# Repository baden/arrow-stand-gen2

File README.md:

# arrow-stand-gen2 — бездрововий датчик влучання в мішень

Пристрій, що кріпиться на мішень, фіксує удар (акселерометр), і бездрово передає
факт влучання на базову станцію (приймач) за LoRa.

**Мета проєкту — мінімально можлива собівартість.** Пристрій розхідний: він
отримує удари і, можливо, знищується під час стрільби. Тому критерії відбору
компонентів — не «найкраще», а «дешевше, при цьому працює».

## Поточний стан

| Блок | Статус | Рішення |
|---|---|---|
| Радіо | Обрано | SX1262IMLTRT, 150–960 МГц, +22 dBm, $1.91 @100 шт |
| МК | Обрано | **CH32V203F8U6** (QFN-20), 64 KB Flash / 20 KB SRAM, 144 МГц, $0.39 @100 шт — див. [ADR-0007](docs/adr/0007-mcu-and-radio.md) |
| Акселерометр | Кандидат | SC7A20HTR, ±16 g, LGA-12, $0.20 @100 шт — див. [ADR-0003](docs/adr/0003-accelerometer.md) |
| Живлення | Кандидат | LiPo 3.7 В → ME6211C33M5G-N (3.3 В LDO, $0.051) + TP4056 ($0.148) |
| Антена | Обрано | **SMA + зовнішня антена** (обов'язково для >1 км) — див. [ADR-0004](docs/adr/0004-antenna.md) |
| Прошивка | Не розпочато | RISC-V (WCH), toolchain MounRiver; конвеєр аналізу на пристрої — [ADR-0008](docs/adr/0008-ondevice-analysis-and-hub.md) |
| Хаб | Спроєктовано | те саме залізо: CH32V203F8U6 + SX1262 у RX + USB-C — [ADR-0008](docs/adr/0008-ondevice-analysis-and-hub.md) |
| Частота радіо | Обрано | **433 МГц** — ліс і холми, найкраще проникнення й запас чутливості — див. [ADR-0005](docs/adr/0005-radio-band.md) |

## Орієнтовна собівартість (за 100 шт.)

Ціни — **цінова сходинка LCSC при замовленні 100 шт.** (2026-11-18).

```
PCB 2 шари, 35×40 мм .............. $0.35
SX1262IMLTRT ....................... $1.91
CH32V203F8U6 ....................... $0.39
SC7A20HTR ......................... $0.20
TP4056-42-ESOP8 .................... $0.15
Кристал 32 МГц ..................... $0.10
ME6211C33M5G-N ..................... $0.05
Пасивні (~8 шт) + кнопка ......... $0.06
                                  ─────────
                        Разом:    ≈ $3.21  (без монтажу)
```

Деталі — у [docs/cost/budget.md](docs/cost/budget.md).
Зняття цін: `python3 tools/lcsc_prices.py --from-bom hardware/bom/bom-draft.csv --qty 100 --update-bom`.

## Структура репозиторію

```
docs/            документація: вимоги, архітектура, ADR, план дослідження, вартість
                 architecture/schematic-spec.md — специфікація схеми мішені
                 hub/hub-requirements.md   — початкове ТЗ хаба
hardware/        target/ + hub/ (проєкти KiCAD), BOM, механіка, збірка
firmware/        common/ (спільне), target/ (мішень), hub/ (хаб)
tools/           допоміжні скрипти
.opencode/       проєктні скіли та агент для ШІ
```

## Швидкий старт для агента

Прочитай [AGENTS.md](AGENTS.md) — це обов'язковий інструктаж перед будь-якою
роботою в репозиторії. Там же — маршрутизація інструментів Copperpour і
правила «дешево».

## Ліцензії та походження

Компоненти — з LCSC/JLCPCB. Перед серійною парттією перевірити локальні
регуляторні вимоги до діапазону й потужності передавача (ETSI EN 300 220 /
FCC Part 15) та правила літій на зони ураження.

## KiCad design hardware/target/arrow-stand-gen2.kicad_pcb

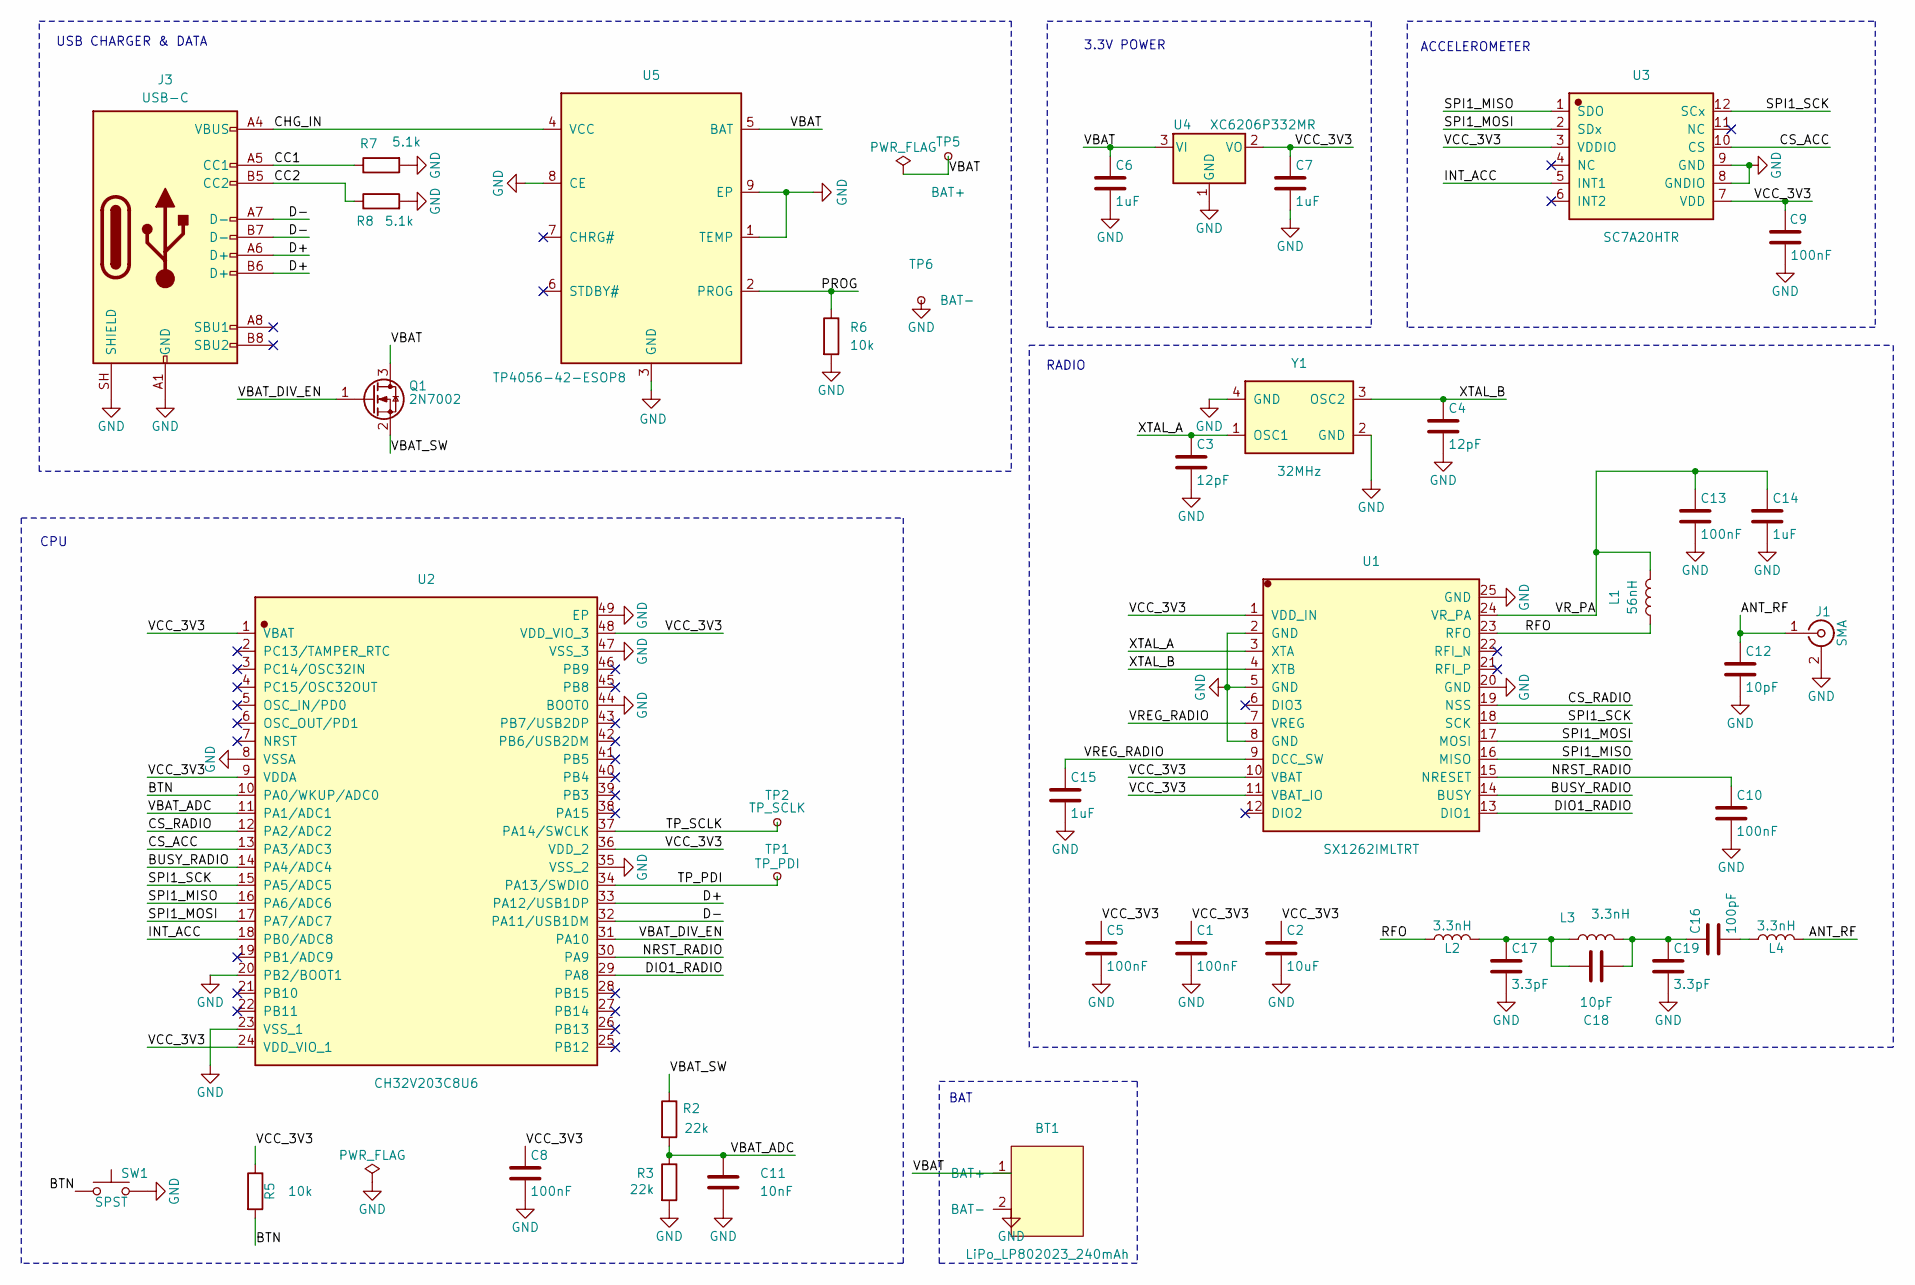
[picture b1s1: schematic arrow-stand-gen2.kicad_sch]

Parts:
BT1: LiPo_LP802023_240mAh; MPN LP802023
C1, C5, C8, C9, C10, C13: 100nF; C_0402_1005Metric; MPN CL05B104KO5NNNC; LCSC C1525
C2: 10uF; C_0805_2012Metric; MPN CL21A106KAYNNNE; LCSC C15850
C3, C4: 12pF; C_0402_1005Metric; MPN 0402CG120J500NT; LCSC C1547
C6, C7, C14, C15: 1uF; C_0402_1005Metric; MPN CL05A105KA5NQNC; LCSC C52923
C11: 10nF; C_0402_1005Metric; MPN CL05B103KB5NNNC; LCSC C15195
C12, C18: 10pF; C_0402_1005Metric; MPN CL05C100JB5NNNC; LCSC C32949
C16: 100pF; C_0402_1005Metric; MPN 0402CG101J500NT; LCSC C1546
C17, C19: 3.3pF; C_0402_1005Metric; MPN 0402CG3R3C500NT; LCSC C1565
J1: SMA; SMA_Amphenol_132134_Vertical; MPN HL-SMA-KE-02; LCSC C20617215
J3: USB-C; USB_C_Receptacle_HRO_TYPE-C-31-M-12; MPN TYPE-C-31-M-12; LCSC C165948
L1: 56nH; L_0402_1005Metric; MPN LQW15AN56NG80D; LCSC C1330587
L2, L3, L4: 3.3nH; L_0402_1005Metric; MPN VHF100505HQ3N3BT; LCSC C3032779
Q1: 2N7002; SOT-23; MPN 2N7002; LCSC C8545
R2, R3: 22k; R_0402_1005Metric; MPN 0402WGF2202TCE; LCSC C25768
R5, R6: 10k; R_0402_1005Metric; MPN 0402WGF1002TCE; LCSC C25744
R7, R8: 5.1k; R_0402_1005Metric; MPN 0402WGF5101TCE; LCSC C25905
SW1: SPST; SW_SPST_B3U-1000P; MPN B3U-1000P; LCSC C231329
TP1: TP_PDI; TestPoint_Pad_1.0x1.0mm
TP2: TP_SCLK; TestPoint_Pad_1.0x1.0mm
TP5: BAT+; TestPoint_Pad_1.0x1.0mm
TP6: BAT-; TestPoint_Pad_1.0x1.0mm
U1: SX1262IMLTRT; QFN-24_L4.0-W4.0-P0.50-BL-EP2.6; MPN SX1262IMLTRT; JLCPCB_Class Extended Part
U2: CH32V203C8U6; TQFN-48_L7.0-W7.0-P0.50-BL-EP5.5; MPN CH32V203C8U6; JLCPCB_Class Extended Part
U3: SC7A20HTR; LGA-12_L2.0-W2.0-P0.50-TL; MPN SC7A20HTR; JLCPCB_Class Extended Part
U4: XC6206P332MR; SOT-23-3; MPN XC6206P332MR; LCSC C2897477
U5: TP4056-42-ESOP8; ESOP-8_L4.9-W3.9-P1.27-LS6.0-BL-EP; MPN TP4056-42-ESOP8; JLCPCB_Class Extended Part
Y1: 32MHz; CRYSTAL-SMD_4P-L3.2-W2.5-BL; MPN E3SB32E00000KE; JLCPCB_Class Extended Part

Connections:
/ANT_RF: C12.1, J1.1 (In), L4.2
/BTN: R5.2, SW1.1, U2.10 (PA0/WKUP/ADC0)
/BUSY_RADIO: U1.14 (BUSY), U2.14 (PA4/ADC4)
/CC1: J3.A5 (CC1), R7.1
/CC2: J3.B5 (CC2), R8.1
/CHG_IN: J3.A4 (VBUS), J3.A9 (VBUS), J3.B4 (VBUS), J3.B9 (VBUS), U5.4 (VCC)
/CS_ACC: U2.13 (PA3/ADC3), U3.10 (CS)
/CS_RADIO: U1.19 (NSS), U2.12 (PA2/ADC2)
/D+: J3.A6 (D+), J3.B6 (D+), U2.33 (PA12/USB1DP)
/D-: J3.A7 (D-), J3.B7 (D-), U2.32 (PA11/USB1DM)
/DIO1_RADIO: U1.13 (DIO1), U2.29 (PA8)
/INT_ACC: U2.18 (PB0/ADC8), U3.5 (INT1)
/NRST_RADIO: C10.1, U1.15 (NRESET), U2.30 (PA9)
/PROG: R6.1, U5.2 (PROG)
/RFO: L1.2, L2.1, U1.23 (RFO)
/SPI1_MISO: U1.16 (MISO), U2.16 (PA6/ADC6), U3.1 (SDO)
/SPI1_MOSI: U1.17 (MOSI), U2.17 (PA7/ADC7), U3.2 (SDx)
/SPI1_SCK: U1.18 (SCK), U2.15 (PA5/ADC5), U3.12 (SCx)
/TP_PDI: TP1.1 (1_1), U2.34 (PA13/SWDIO)
/TP_SCLK: TP2.1 (1_1), U2.37 (PA14/SWCLK)
/VBAT: BT1.1 (BAT+), C6.1, Q1.3 (D), TP5.1 (1_1), U4.3 (VI), U5.5 (BAT)
/VBAT_ADC: C11.1, R2.2, R3.1, U2.11 (PA1/ADC1)
/VBAT_DIV_EN: Q1.1 (G), U2.31 (PA10)
/VBAT_SW: Q1.2 (S), R2.1
/VCC_3V3: C1.1, C2.1, C5.1, C7.1, C8.1, C9.1, R5.1, U1.1 (VDD_IN), U1.10 (VBAT), U1.11 (VBAT_IO), U2.1 (VBAT), U2.9 (VDDA), U2.24 (VDD_VIO_1), U2.36 (VDD_2), U2.48 (VDD_VIO_3), U3.3 (VDDIO), U3.7 (VDD), U4.2 (VO)
/VREG_RADIO: C15.1, U1.7 (VREG), U1.9 (DCC_SW)
/VR_PA: C13.1, C14.1, L1.1, U1.24 (VR_PA)
/XTAL_A: C3.1, U1.3 (XTA), Y1.1 (OSC1)
/XTAL_B: C4.1, U1.4 (XTB), Y1.3 (OSC2)
GND: BT1.2 (BAT-), C1.2, C2.2, C3.2, C4.2, C5.2, C6.2, C7.2, C8.2, C9.2, C10.2, C11.2, C12.2, C13.2, C14.2, C15.2, C17.2, C19.2, J1.2 (Ext), J3.A1 (GND), J3.A12 (GND), J3.B1 (GND), J3.B12 (GND), J3.SH (SHIELD), R3.2, R6.2, R7.2, R8.2, SW1.2, TP6.1 (1_1), U1.2 (GND), U1.5 (GND), U1.8 (GND), U1.20 (GND), U1.25 (GND), U2.8 (VSSA), U2.20 (PB2/BOOT1), U2.23 (VSS_1), U2.35 (VSS_2), U2.44 (BOOT0), U2.47 (VSS_3), U2.49 (EP), U3.8 (GNDIO), U3.9 (GND), U4.1 (GND), U5.1 (TEMP), U5.3 (GND), U5.8 (CE), U5.9 (EP), Y1.2 (GND), Y1.4 (GND)
unnamed: C16.1, C18.2, C19.1, L3.2
unnamed: C16.2, L4.1
unnamed: C17.1, C18.1, L2.2, L3.1

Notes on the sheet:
BAT
3.3V POWER
CPU
ACCELEROMETER
RADIO
USB CHARGER & DATA

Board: 2 copper layers, 44 parts (0 on the bottom side), 33 nets, no tracks yet.

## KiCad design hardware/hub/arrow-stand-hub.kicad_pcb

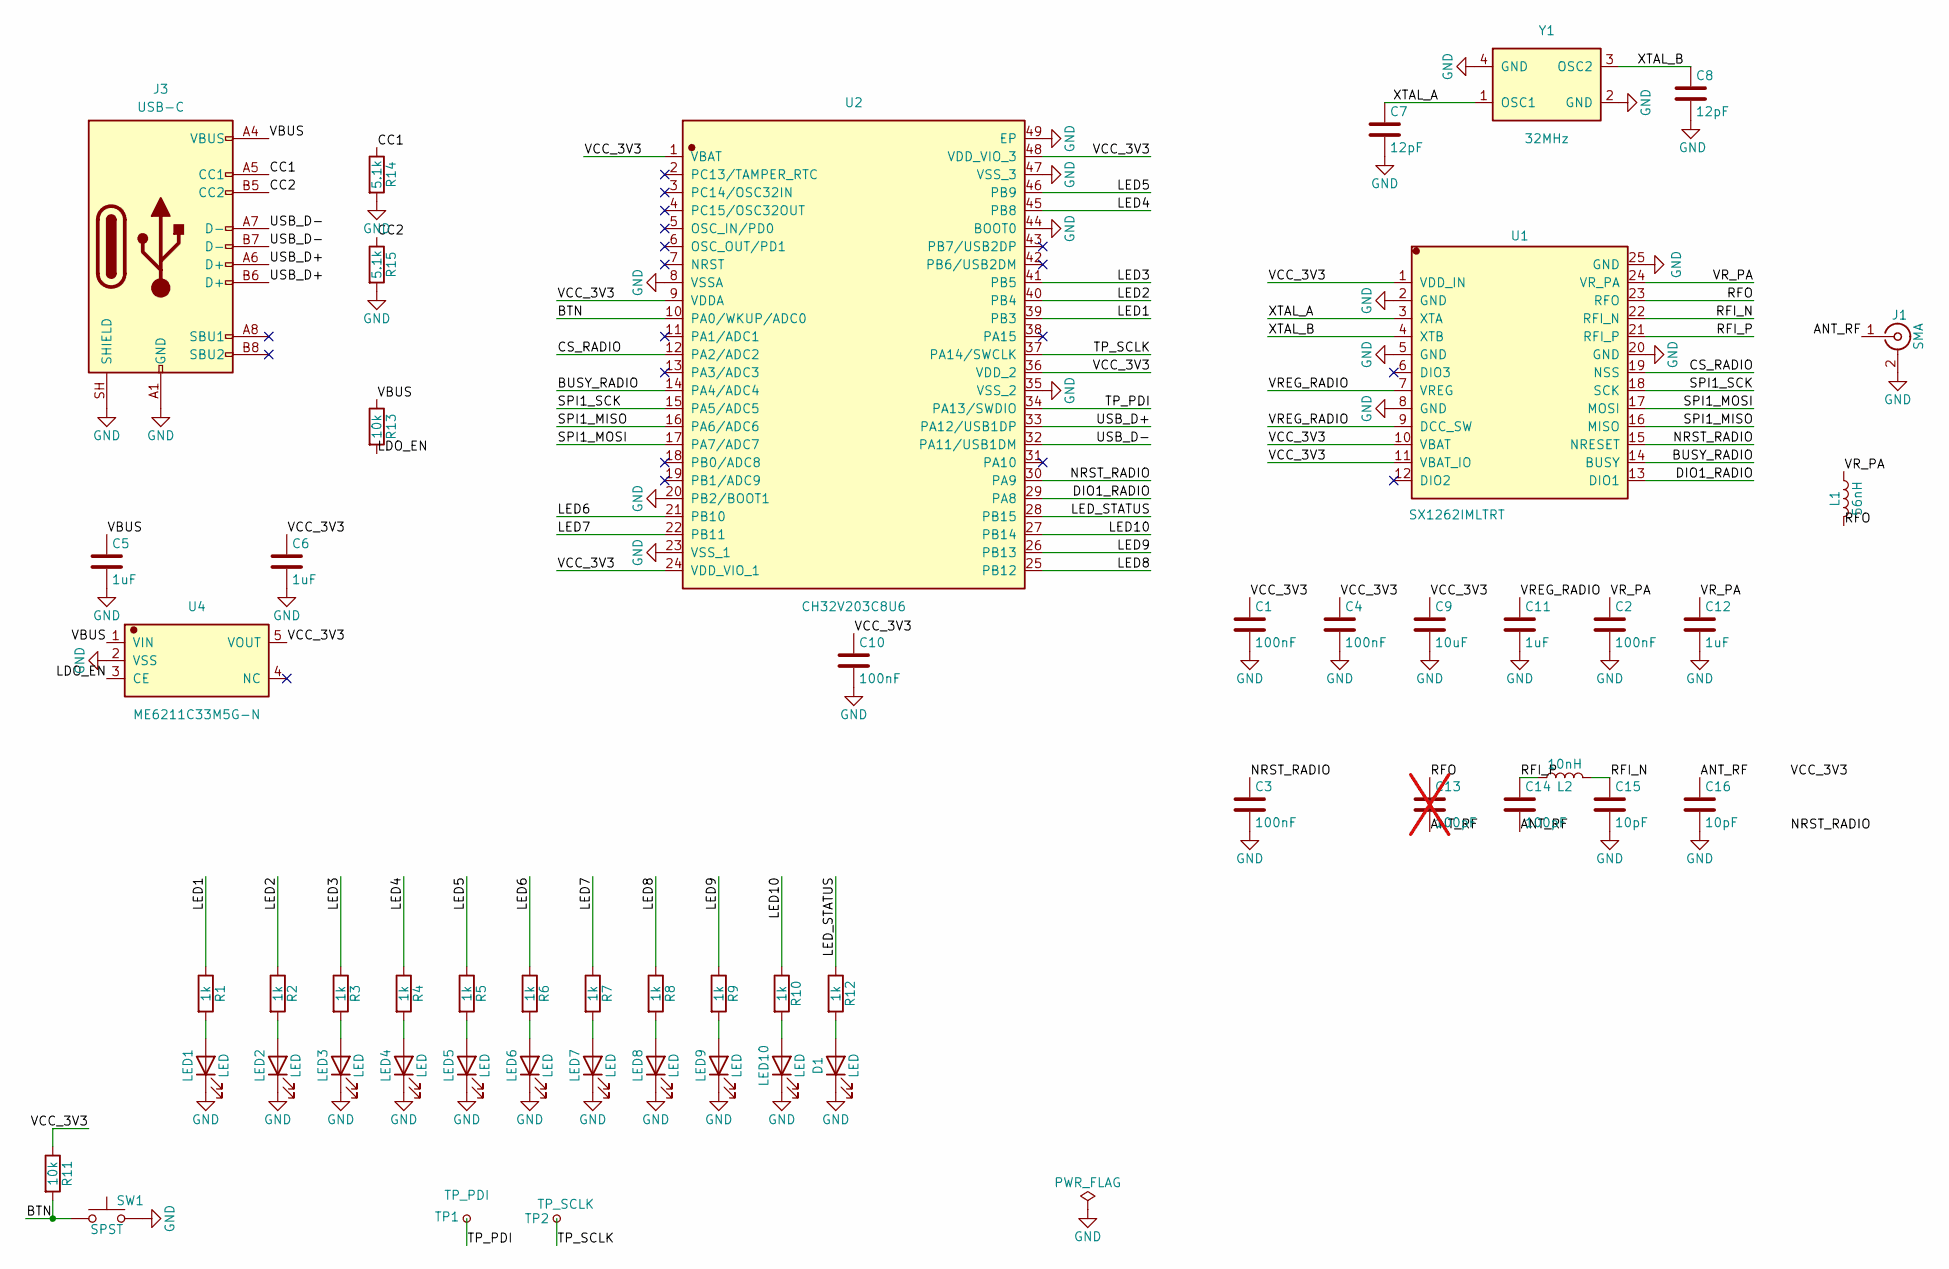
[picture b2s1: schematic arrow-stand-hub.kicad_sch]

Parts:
C1, C3, C4, C10: 100nF; C_0402_1005Metric; MPN CL05B104KO5NNNC; LCSC C1525
C2: 100nF; C_0402_1005Metric
C5, C6, C11, C12: 1uF; C_0402_1005Metric; MPN CL05A105KA5NQNC; LCSC C52923
C7, C8: 12pF; C_0402_1005Metric; MPN 0402CG120J500NT; LCSC C1547
C9: 10uF; C_0805_2012Metric; MPN CL21A106KAYNNNE; LCSC C15850
C13: 100pF; C_0402_1005Metric; MPN 0402CG101J500NT; LCSC C1546; not fitted
C14: 100pF; C_0402_1005Metric; MPN 0402CG101J500NT; LCSC C1546
C15, C16: 10pF; C_0402_1005Metric; MPN CL05C100JB5NNNC; LCSC C32949
D1: LED; LED_0805_2012Metric; MPN D-G080508G1-KS2; LCSC C107402
J1: SMA; SMA_Amphenol_132289_EdgeMount
J3: USB-C; USB_C_Receptacle_HRO_TYPE-C-31-M-12; MPN TYPE-C-31-M-12; LCSC C165948
L1: 56nH; L_0402_1005Metric
L2: 10nH; L_0402_1005Metric; MPN VHF100505HQ10NJT; LCSC C395047
LED1, LED2, LED3, LED4, LED5, LED6, LED7, LED8, LED9, LED10: LED; LED_0805_2012Metric; MPN D-G080508G1-KS2; LCSC C107402
R1, R2, R3, R4, R5, R6, R7, R8, R9, R10, R12: 1k; R_0402_1005Metric; MPN CR0402FF1001G; LCSC C100195
R11, R13: 10k; R_0402_1005Metric; MPN 0402WGF1002TCE; LCSC C25744
R14, R15: 5.1k; R_0402_1005Metric; MPN 0402WGF5101TCE; LCSC C25905
SW1: SPST; SW_SPST_B3U-1000P
TP1: TP_PDI; TestPoint_Pad_1.0x1.0mm
TP2: TP_SCLK; TestPoint_Pad_1.0x1.0mm
U1: SX1262IMLTRT; QFN-24_L4.0-W4.0-P0.50-BL-EP2.6; MPN SX1262IMLTRT; JLCPCB_Class Extended Part
U2: CH32V203C8U6; TQFN-48_L7.0-W7.0-P0.50-BL-EP5.5; MPN CH32V203C8U6; JLCPCB_Class Extended Part
U4: ME6211C33M5G-N; SOT-23-5_L3.0-W1.7-P0.95-LS2.8-BL; MPN ME6211C33M5G-N; JLCPCB_Class Extended Part
Y1: 32MHz; CRYSTAL-SMD_4P-L3.2-W2.5-BL; MPN E3SB32E00000KE; JLCPCB_Class Extended Part

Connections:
/ANT_RF: C13.2, C14.2, C16.1, J1.1 (In)
/BTN: R11.2, SW1.1, U2.10 (PA0/WKUP/ADC0)
/BUSY_RADIO: U1.14 (BUSY), U2.14 (PA4/ADC4)
/CC1: J3.A5 (CC1), R14.1
/CC2: J3.B5 (CC2), R15.1
/CS_RADIO: U1.19 (NSS), U2.12 (PA2/ADC2)
/DIO1_RADIO: U1.13 (DIO1), U2.29 (PA8)
/LDO_EN: R13.2, U4.3 (CE)
/LED1: R1.1, U2.39 (PB3)
/LED2: R2.1, U2.40 (PB4)
/LED3: R3.1, U2.41 (PB5)
/LED4: R4.1, U2.45 (PB8)
/LED5: R5.1, U2.46 (PB9)
/LED6: R6.1, U2.21 (PB10)
/LED7: R7.1, U2.22 (PB11)
/LED8: R8.1, U2.25 (PB12)
/LED9: R9.1, U2.26 (PB13)
/LED10: R10.1, U2.27 (PB14)
/LED_STATUS: R12.1, U2.28 (PB15)
/NRST_RADIO: C3.1, U1.15 (NRESET), U2.30 (PA9); also elsewhere on the board
/RFI_N: C15.1, L2.2, U1.22 (RFI_N)
/RFI_P: C14.1, L2.1, U1.21 (RFI_P)
/RFO: C13.1, L1.2, U1.23 (RFO)
/SPI1_MISO: U1.16 (MISO), U2.16 (PA6/ADC6)
/SPI1_MOSI: U1.17 (MOSI), U2.17 (PA7/ADC7)
/SPI1_SCK: U1.18 (SCK), U2.15 (PA5/ADC5)
/TP_PDI: TP1.1 (1_1), U2.34 (PA13/SWDIO)
/TP_SCLK: TP2.1 (1_1), U2.37 (PA14/SWCLK)
/USB_D+: J3.A6 (D+), J3.B6 (D+), U2.33 (PA12/USB1DP)
/USB_D-: J3.A7 (D-), J3.B7 (D-), U2.32 (PA11/USB1DM)
/VBUS: C5.1, J3.A4 (VBUS), J3.A9 (VBUS), J3.B4 (VBUS), J3.B9 (VBUS), R13.1, U4.1 (VIN)
/VCC_3V3: C1.1, C4.1, C6.1, C9.1, C10.1, R11.1, U1.1 (VDD_IN), U1.10 (VBAT), U1.11 (VBAT_IO), U2.1 (VBAT), U2.9 (VDDA), U2.24 (VDD_VIO_1), U2.36 (VDD_2), U2.48 (VDD_VIO_3), U4.5 (VOUT); also elsewhere on the board
/VREG_RADIO: C11.1, U1.7 (VREG), U1.9 (DCC_SW)
/VR_PA: C2.1, C12.1, L1.1, U1.24 (VR_PA)
/XTAL_A: C7.1, U1.3 (XTA), Y1.1 (OSC1)
/XTAL_B: C8.1, U1.4 (XTB), Y1.3 (OSC2)
GND: C1.2, C2.2, C3.2, C4.2, C5.2, C6.2, C7.2, C8.2, C9.2, C10.2, C11.2, C12.2, C15.2, C16.2, D1.1 (K), J1.2 (Ext), J3.A1 (GND), J3.A12 (GND), J3.B1 (GND), J3.B12 (GND), J3.SH (SHIELD), LED1.1 (K), LED2.1 (K), LED3.1 (K), LED4.1 (K), LED5.1 (K), LED6.1 (K), LED7.1 (K), LED8.1 (K), LED9.1 (K), LED10.1 (K), R14.2, R15.2, SW1.2, U1.2 (GND), U1.5 (GND), U1.8 (GND), U1.20 (GND), U1.25 (GND), U2.8 (VSSA), U2.20 (PB2/BOOT1), U2.23 (VSS_1), U2.35 (VSS_2), U2.44 (BOOT0), U2.47 (VSS_3), U2.49 (EP), U4.2 (VSS), Y1.2 (GND), Y1.4 (GND)
unnamed: D1.2 (A), R12.2
unnamed: LED1.2 (A), R1.2
unnamed: LED2.2 (A), R2.2
unnamed: LED3.2 (A), R3.2
unnamed: LED4.2 (A), R4.2
unnamed: LED5.2 (A), R5.2
unnamed: LED6.2 (A), R6.2
unnamed: LED7.2 (A), R7.2
unnamed: LED8.2 (A), R8.2
unnamed: LED9.2 (A), R9.2
unnamed: LED10.2 (A), R10.2

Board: 2 copper layers, 54 parts (0 on the bottom side), 48 nets, no tracks yet.

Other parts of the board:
R16: 100k; R_0402_1005Metric

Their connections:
/NRST_RADIO: R16.2; also elsewhere on the board
/VCC_3V3: R16.1; also elsewhere on the board
